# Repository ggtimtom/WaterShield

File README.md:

# WaterShield
Pi Shield für die Gartenbewässerung

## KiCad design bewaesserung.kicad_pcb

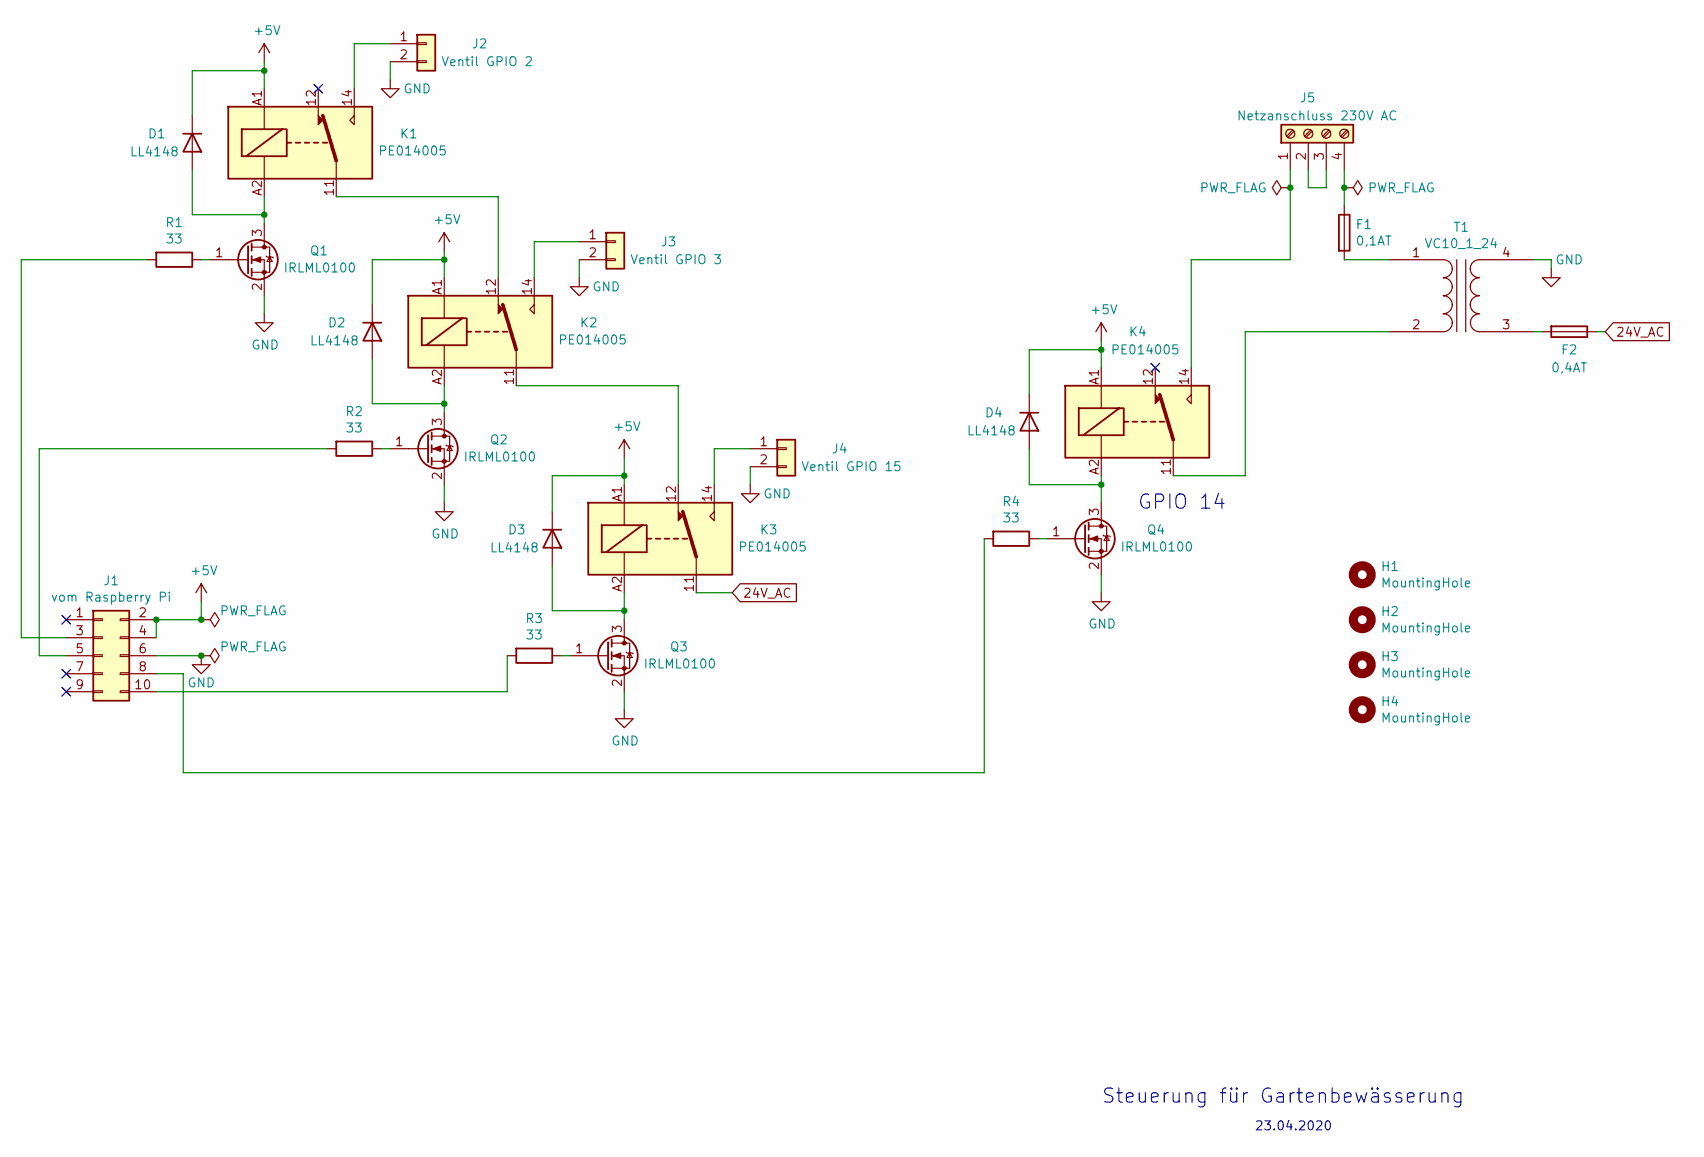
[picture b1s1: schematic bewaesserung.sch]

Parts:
D1, D2, D3, D4: LL4148; D_MiniMELF
F1: 0,1AT; Fuse_TR5
F2: 0,4AT; Fuse_TR5
H1, H2, H3, H4: MountingHole; MountingHole_3.2mm_M3_DIN965
J1: vom Raspberry Pi; IDC-Header_2x05_P2.54mm_Vertical
J2: Ventil GPIO 2; PSS2542-2G
J3: Ventil GPIO 3; PSS2542-2G
J4: Ventil GPIO 15; PSS2542-2G
J5: Netzanschluss 230V AC; Schraubklemme_4-fach
K1, K2, K3, K4: PE014005
Q1, Q2, Q3, Q4: IRLML0100; SOT-23
R1, R2, R3, R4: 33; R_1206_3216Metric
T1: VC10_1_24

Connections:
24V_AC: F2.1, K3.11
+5V: D1.1 (K), D2.1 (K), D3.1 (K), D4.1 (K), J1.2, J1.4, K1.A1, K2.A1, K3.A1, K4.A1
GND: J1.6, J2.2, J3.2, J4.2, Q1.2 (S), Q2.2 (S), Q3.2 (S), Q4.2 (S), T1.4 (SB)
unnamed: D1.2 (A), K1.A2, Q1.3 (D)
unnamed: D2.2 (A), K2.A2, Q2.3 (D)
unnamed: D3.2 (A), K3.A2, Q3.3 (D)
unnamed: D4.2 (A), K4.A2, Q4.3 (D)
unnamed: F1.1, J5.4
unnamed: F1.2, T1.1 (AA)
unnamed: F2.2, T1.3 (SA)
unnamed: J1.3, R1.2
unnamed: J1.5, R2.2
unnamed: J1.8, R4.2
unnamed: J1.10, R3.2
unnamed: J2.1, K1.14
unnamed: J3.1, K2.14
unnamed: J4.1, K3.14
unnamed: J5.1, K4.14
unnamed: J5.2, J5.3
unnamed: K1.11, K2.12
unnamed: K2.11, K3.12
unnamed: K4.11, T1.2 (AB)
unnamed: Q1.1 (G), R1.1
unnamed: Q2.1 (G), R2.1
unnamed: Q3.1 (G), R3.1
unnamed: Q4.1 (G), R4.1

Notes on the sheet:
23.04.2020
Steuerung für Gartenbewässerung
GPIO 14

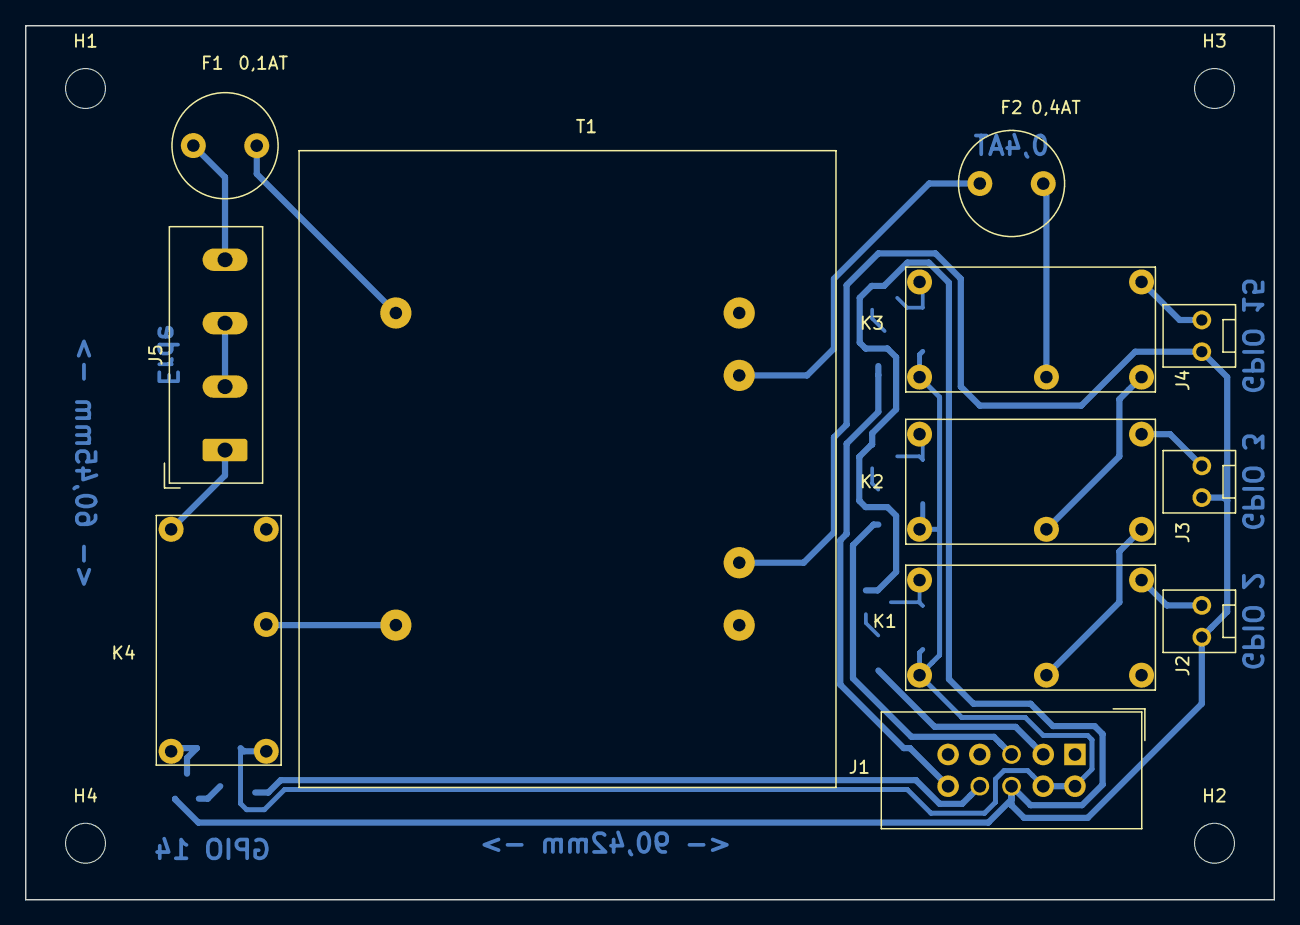
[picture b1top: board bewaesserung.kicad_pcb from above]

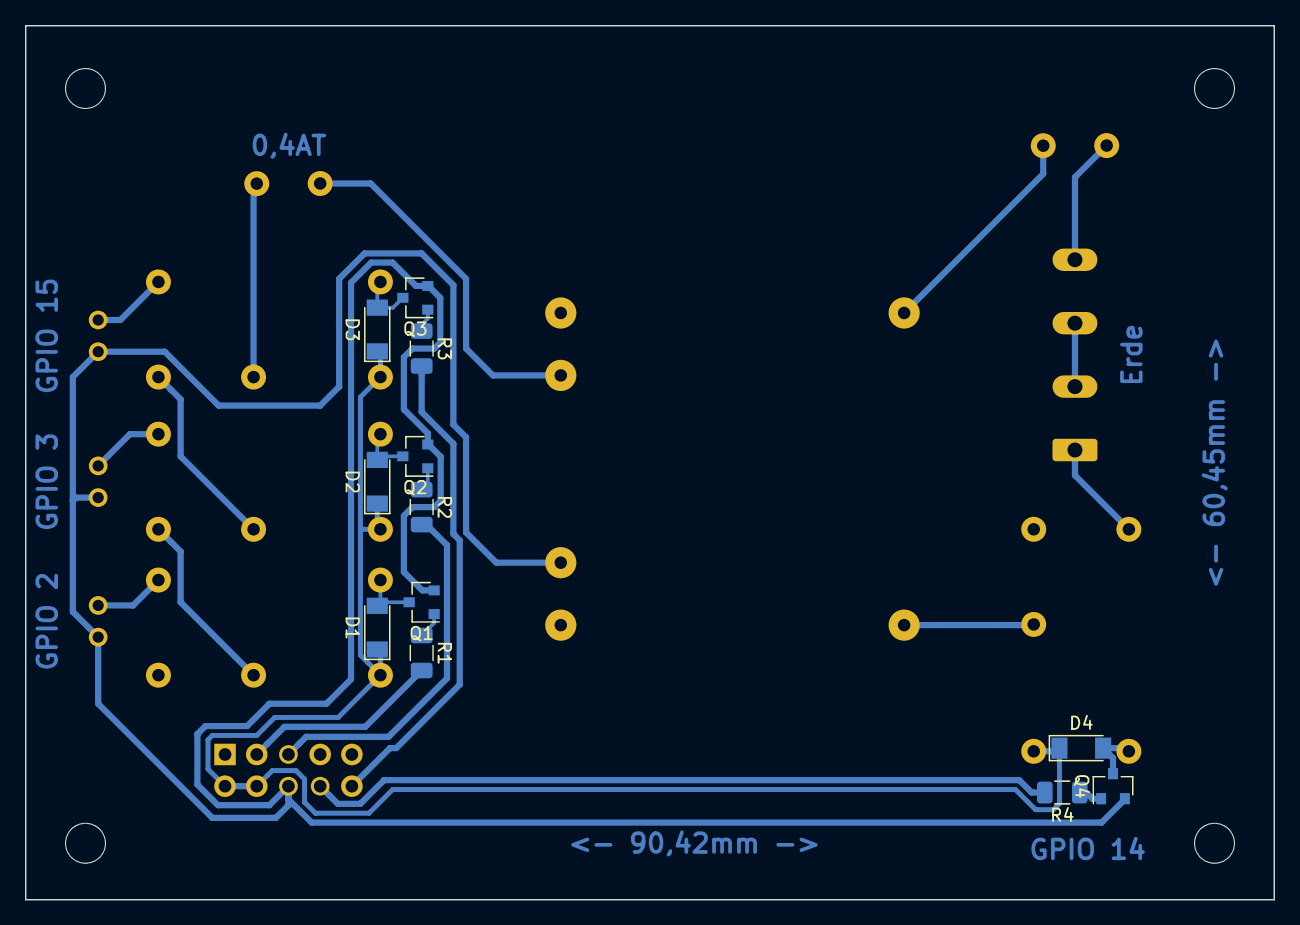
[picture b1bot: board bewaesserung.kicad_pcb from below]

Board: 2 copper layers, 100.0 x 70.0 mm, 28 parts (12 on the bottom side), 26 nets.

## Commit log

2020-04-29 initiale Version
2020-05-01 Sicherungen angepasst
